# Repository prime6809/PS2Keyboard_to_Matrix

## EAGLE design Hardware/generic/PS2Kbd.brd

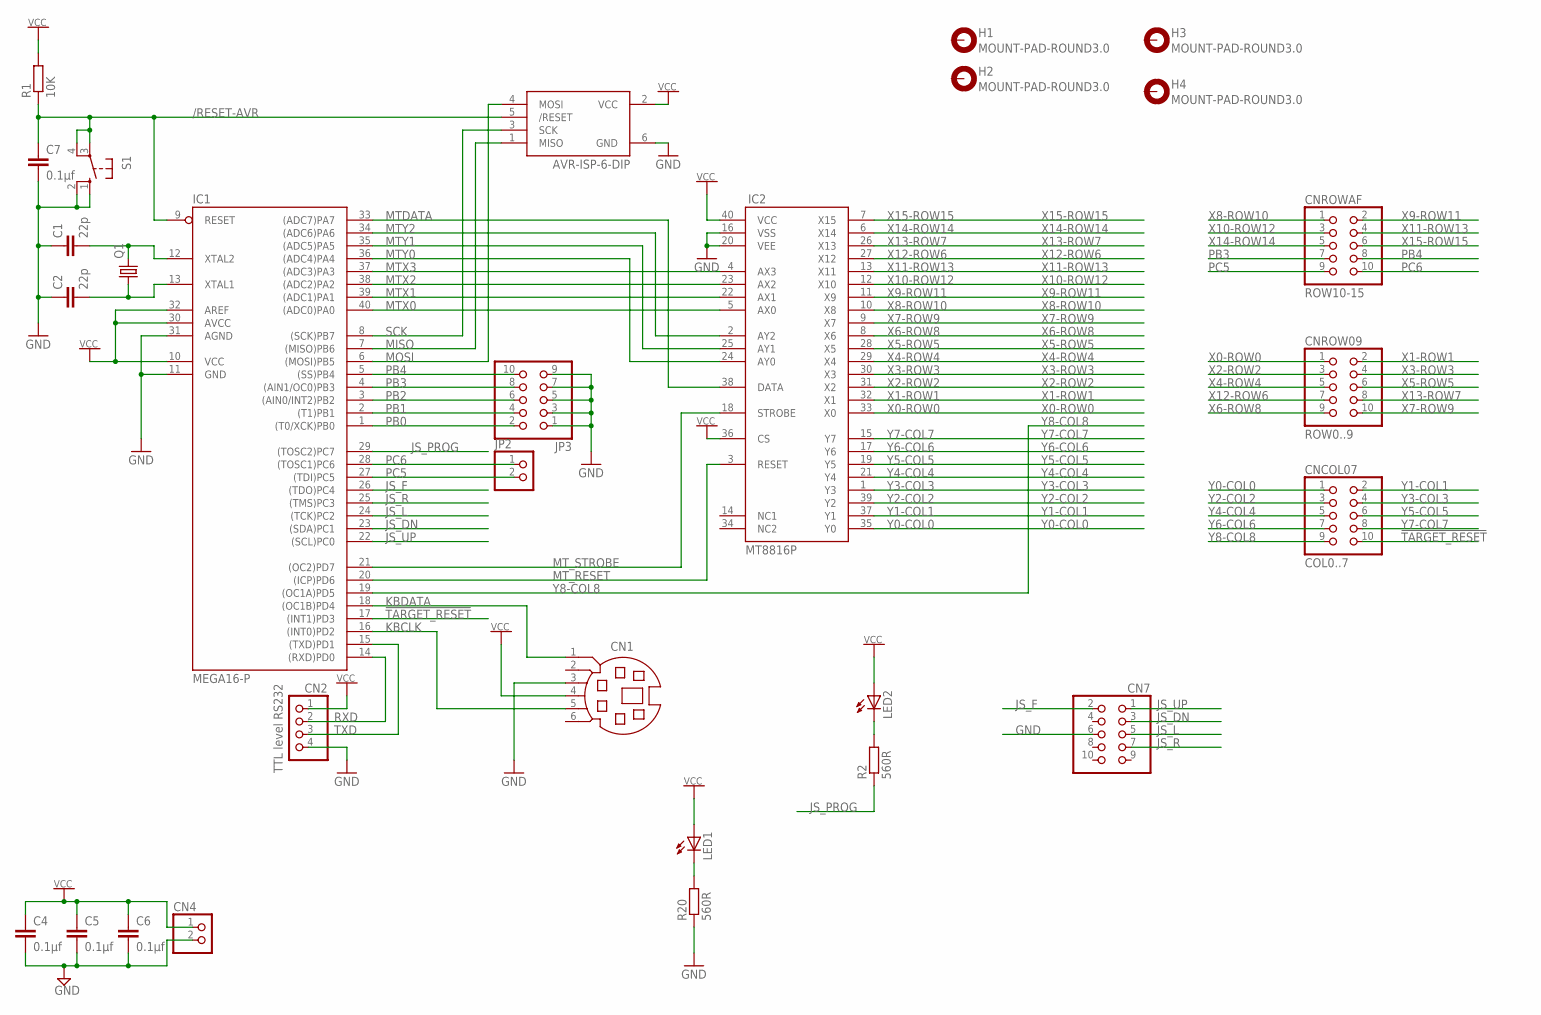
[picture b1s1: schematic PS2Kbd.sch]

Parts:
C1, C2: 22p; C025-025X050
C4, C5, C6, C7: 0.1µf; C025-025X050
CN1: MD06SS; MDIN06SS
CN2: PINHD-1X4; 1X04
CN3: AVR-ISP-6-DIP; 2X3
CN4: PINHD-1X2; 1X02
CN7: PINHD-2X5; 2X05
CNCOL07: COL0..7; 2X05
CNROW09: ROW0..9; 2X05
CNROWAF: ROW10-15; 2X05
H1, H2, H3, H4: MOUNT-PAD-ROUND3.0; 3,0-PAD
IC1: MEGA16-P; DIL40
IC2: MT8816P; DIL40
JP2: PINHD-1X2; 1X02
JP3: PINHD-2X5; 2X05
LED1, LED2: LED3MM
Q1: CRYSTALHC49S; HC49/S
R1: 10K; 0207/10
R2, R20: 560R; 0207/10
S1: 10-XX; B3F-10XX

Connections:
!TARGET_RESET: CNCOL07.10, IC1.17 ((INT1)PD3)
/RESET-AVR: C7.1, CN3.5 (/RESET), IC1.9 (RESET), R1.1, S1.3, S1.4 (P1)
GND: C1.1, C2.1, C4.2, C5.2, C6.2, C7.2, CN1.3, CN2.4, CN3.6 (GND), CN4.2, CN7.6, IC1.11 (GND), IC1.31 (AGND), IC2.16 (VSS), IC2.20 (VEE), JP3.1, JP3.3, JP3.5, JP3.7, JP3.9, R20.1, S1.1 (S), S1.2 (S1)
JS_DN: CN7.3, IC1.23 ((SDA)PC1)
JS_F: CN7.2, IC1.26 ((TDO)PC4)
JS_L: CN7.5, IC1.24 ((TCK)PC2)
JS_PROG: IC1.29 ((TOSC2)PC7), R2.1
JS_R: CN7.7, IC1.25 ((TMS)PC3)
JS_UP: CN7.1, IC1.22 ((SCL)PC0)
KBCLK: CN1.5, IC1.16 ((INT0)PD2)
KBDATA: CN1.1, IC1.18 ((OC1B)PD4)
MISO: CN3.1 (MISO), IC1.7 ((MISO)PB6)
MOSI: CN3.4 (MOSI), IC1.6 ((MOSI)PB5)
MTDATA: IC1.33 ((ADC7)PA7), IC2.38 (DATA)
MTX0: IC1.40 ((ADC0)PA0), IC2.5 (AX0)
MTX1: IC1.39 ((ADC1)PA1), IC2.22 (AX1)
MTX2: IC1.38 ((ADC2)PA2), IC2.23 (AX2)
MTX3: IC1.37 ((ADC3)PA3), IC2.4 (AX3)
MTY0: IC1.36 ((ADC4)PA4), IC2.24 (AY0)
MTY1: IC1.35 ((ADC5)PA5), IC2.25 (AY1)
MTY2: IC1.34 ((ADC6)PA6), IC2.2 (AY2)
MT_RESET: IC1.20 ((ICP)PD6), IC2.3 (RESET)
MT_STROBE: IC1.21 ((OC2)PD7), IC2.18 (STROBE)
unnamed: LED2.K (C), R2.2
unnamed: C1.2, IC1.12 (XTAL2), Q1.2
unnamed: C2.2, IC1.13 (XTAL1), Q1.1
unnamed: LED1.K (C), R20.2
PB0: IC1.1 ((T0/XCK)PB0), JP3.2
PB1: IC1.2 ((T1)PB1), JP3.4
PB2: IC1.3 ((AIN0/INT2)PB2), JP3.6
PB3: CNROWAF.7, IC1.4 ((AIN1/OC0)PB3), JP3.8
PB4: CNROWAF.8, IC1.5 ((SS)PB4), JP3.10
PC5: CNROWAF.9, IC1.27 ((TDI)PC5), JP2.2
PC6: CNROWAF.10, IC1.28 ((TOSC1)PC6), JP2.1
RXD: CN2.2, IC1.14 ((RXD)PD0)
SCK: CN3.3 (SCK), IC1.8 ((SCK)PB7)
TXD: CN2.3, IC1.15 ((TXD)PD1)
VCC: C4.1, C5.1, C6.1, CN1.4, CN2.1, CN3.2 (VCC), CN4.1, IC1.10 (VCC), IC1.30 (AVCC), IC1.32 (AREF), IC2.36 (CS), IC2.40 (VCC), LED1.A, LED2.A, R1.2
X0-ROW0: CNROW09.1, IC2.33 (X0)
X1-ROW1: CNROW09.2, IC2.32 (X1)
X2-ROW2: CNROW09.3, IC2.31 (X2)
X3-ROW3: CNROW09.4, IC2.30 (X3)
X4-ROW4: CNROW09.5, IC2.29 (X4)
X5-ROW5: CNROW09.6, IC2.28 (X5)
X6-ROW8: CNROW09.9, IC2.8 (X6)
X7-ROW9: CNROW09.10, IC2.9 (X7)
X8-ROW10: CNROWAF.1, IC2.10 (X8)
X9-ROW11: CNROWAF.2, IC2.11 (X9)
X10-ROW12: CNROWAF.3, IC2.12 (X10)
X11-ROW13: CNROWAF.4, IC2.13 (X11)
X12-ROW6: CNROW09.7, IC2.27 (X12)
X13-ROW7: CNROW09.8, IC2.26 (X13)
X14-ROW14: CNROWAF.5, IC2.6 (X14)
X15-ROW15: CNROWAF.6, IC2.7 (X15)
Y0-COL0: CNCOL07.1, IC2.35 (Y0)
Y1-COL1: CNCOL07.2, IC2.37 (Y1)
Y2-COL2: CNCOL07.3, IC2.39 (Y2)
Y3-COL3: CNCOL07.4, IC2.1 (Y3)
Y4-COL4: CNCOL07.5, IC2.21 (Y4)
Y5-COL5: CNCOL07.6, IC2.19 (Y5)
Y6-COL6: CNCOL07.7, IC2.17 (Y6)
Y7-COL7: CNCOL07.8, IC2.15 (Y7)
Y8-COL8: CNCOL07.9, IC1.19 ((OC1A)PD5)

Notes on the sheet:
TTL level RS232

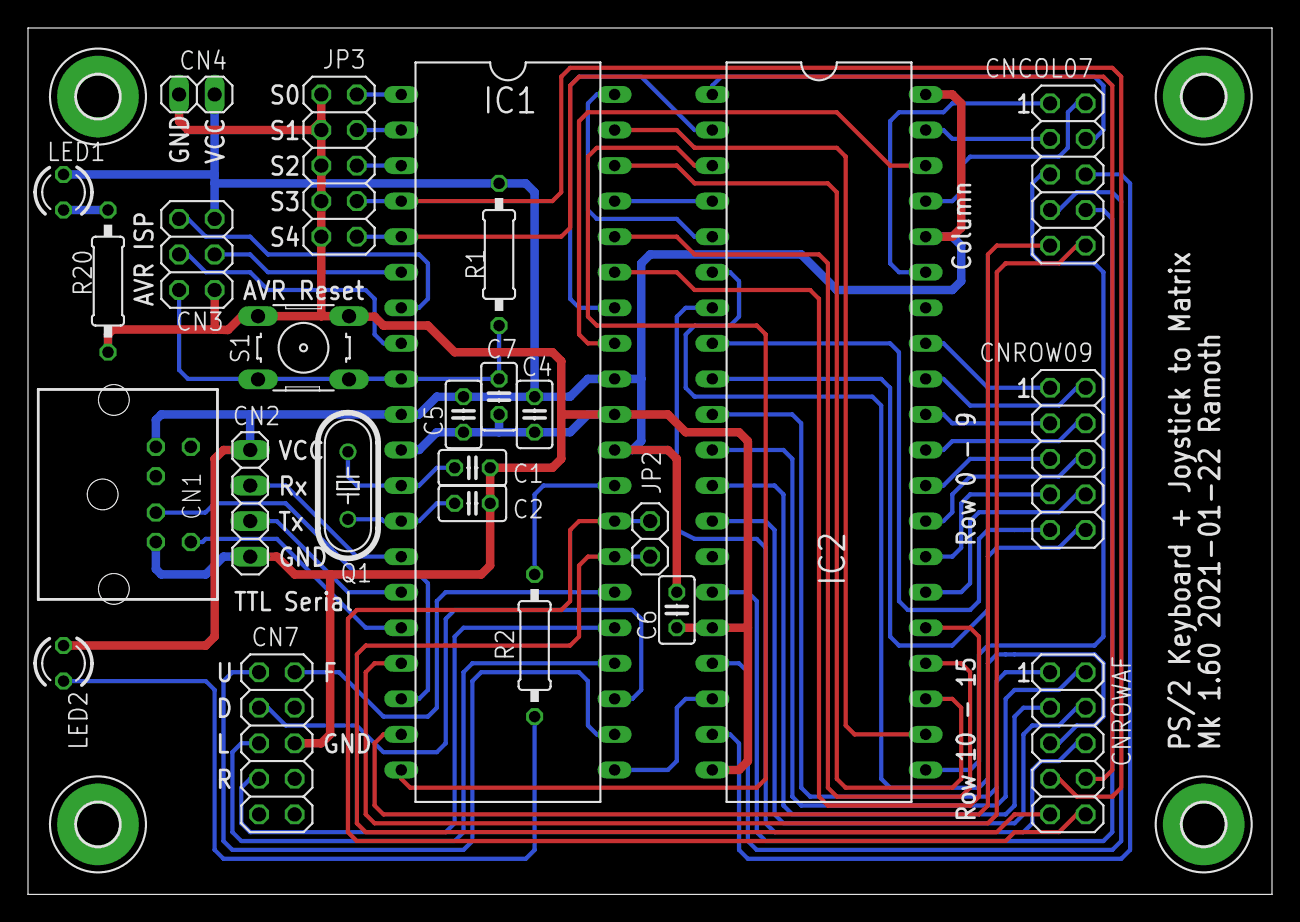
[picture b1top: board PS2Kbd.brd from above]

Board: 2 copper layers, 88.9 x 61.9 mm, 29 parts (0 on the bottom side), 63 nets.

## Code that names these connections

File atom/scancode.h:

/*
	Scancode table for the AtomClone keyboard interface. 

 PCScanCodeTo Acorn Atom keyboard emulation routines.

 Adapted from PCScanCodeTo Dragon, P.Harvey-Smith, 2008-12-06.
 
 The Atom keyboard data is then output to a Zarlink MT8816 8x16 
 crosspoint switch.

 The outputs of this crosspoint switch are then connected to the 
 Atom Row and column inputs, which are scanned by the Atom's 8255
 using port B1..7 (and C6) as pulled up inputs, and port A0..3
 as outputs connected to a 74LS45 or 74LS145, to select the row 
 to scan. This gives 10 rows and 9 columns, however, the 9th
 column only has one key connected to it, which is either grounded
 or pulled up (the REPT key), so this can just be driven by a spare
 AVR IO line.

 As the Atom has 10 rows, these will be connected to X0..9 of the 
 MT8816, and the columns to Y0..7 (and an IO line).

 The Atom keyboard is laid out as follows :-

74LS145	Keyboard columns								
Output		PB0		PB1		PB2		PB3		PB4		PB5		PB6		PB7 	PC6
0			        3		-		G		Q		Esc			
1			        2		,		F		P		Z			
2			U/D		1		;		E		O		Y			
3			L/R		0		:		D		N		X			
4			Lock	Del		9		C		M		W			
5			^		Copy	8		B		L		V			
6			]		Enter	7		A		K		U			
7			\				6		@		J		T			
8			[				5		/		I		S			
9			spc				4		.		H		R			
 									
 GND														Ctrl	Shift	Rept

Fot the following key definition constants, the high nibble and 0x70 represent the 
ROW of the pressed key, and the low nibble represents the COLUMN. Bit 7 is ignored, 
as this is used by the matrix handling code to flag a key pressed or released.
*/

#ifndef __SCANCODES__
#define __SCANCODES__

#include <inttypes.h>
#include <avr/pgmspace.h> 
#include "ps2scancode.h"
#include "matrix_kbd.h"

#define ATOM_KEY_UD			0x02
#define ATOM_KEY_LR			0x03
#define ATOM_KEY_LOCK		0x04
#define ATOM_KEY_CLARET		0x05
#define ATOM_KEY_RBRACK		0x06
#define ATOM_KEY_BSLASH		0x07
#define ATOM_KEY_LBRACK		0x08
#define ATOM_KEY_SPACE		0x09

#define ATOM_KEY_3			0x10
#define ATOM_KEY_2			0x11
#define ATOM_KEY_1			0x12
#define ATOM_KEY_0			0x13
#define ATOM_KEY_DELETE		0x14
#define ATOM_KEY_COPY		0x15
#define ATOM_KEY_ENTER		0x16

#define ATOM_KEY_MINUS		0x20
#define ATOM_KEY_COMMA		0x21
#define ATOM_KEY_SEMICOLON 	0x22
#define ATOM_KEY_COLON 		0x23
#define ATOM_KEY_9 			0x24
#define ATOM_KEY_8 			0x25
#define ATOM_KEY_7 			0x26
#define ATOM_KEY_6 			0x27
#define ATOM_KEY_5 			0x28
#define ATOM_KEY_4 			0x29

#define ATOM_KEY_G 			0x30
#define ATOM_KEY_F 			0x31
#define ATOM_KEY_E 			0x32
#define ATOM_KEY_D 			0x33
#define ATOM_KEY_C 			0x34
#define ATOM_KEY_B 			0x35
#define ATOM_KEY_A 			0x36
#define ATOM_KEY_AT 		0x37
#define ATOM_KEY_SLASH 		0x38
#define ATOM_KEY_POINT 		0x39

#define ATOM_KEY_Q 			0x40
#define ATOM_KEY_P 			0x41
#define ATOM_KEY_O 			0x42
#define ATOM_KEY_N 			0x43
#define ATOM_KEY_M 			0x44
#define ATOM_KEY_L 			0x45
#define ATOM_KEY_K 			0x46
#define ATOM_KEY_J 			0x47
#define ATOM_KEY_I 			0x48
#define ATOM_KEY_H 			0x49

#define ATOM_KEY_ESC 		0x50
#define ATOM_KEY_Z 			0x51
#define ATOM_KEY_Y 			0x52
#define ATOM_KEY_X 			0x53
#define ATOM_KEY_W 			0x54
#define ATOM_KEY_V 			0x55
#define ATOM_KEY_U 			0x56
#define ATOM_KEY_T 			0x57
#define ATOM_KEY_S 			0x58
#define ATOM_KEY_R			0x59

#define ATOM_KEY_CTRL 		0x6A
#define ATOM_KEY_SHIFT 		0x7A
#define ATOM_KEY_REPT 		0x8A

#define ATOM_KEY_BREAK		0xFF

#define SHIFT_KEY	ATOM_KEY_SHIFT
#define RESET_KEY	ATOM_KEY_BREAK


void ScancodeInit(matrix_t *ToInit);
#endif

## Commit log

2021-01-11 Initial commit of source and hardware docs.
2021-01-12 Updated building docs. Revised generic board.
2021-01-12 Test of ssh update, nothing to see here !
2021-01-12 Updated ignore for joe backups
2021-01-12 Fixed typo in building instructions.
2021-01-13 Updated TRS80 and Electron mappings.
2021-01-14 Test commit from work.
2021-01-14 Cleanup / removal of commented (no longer used) code
2021-01-17 Added target commodore, C64, C16, Plus 4, VIC-20. Various internal changes.
2021-01-17 Remove old folder
2021-01-18 Added definitions for numeric keypad for most targets.
2021-01-23 Moved target reset into common code. Implemented centralized initialization of jumpers, joystick and reset. Moved PS/2 LED handling into ps2kbd module. Added macros for setting / clearing LEDS.
2021-01-23 Fixed Dragon / CoCo matrix so all keys are produced. Added matrix dumping code.
2021-01-24 Added matrix dumping function, jumper S4 to enable. Made serial output dependednt on S3 being jumpered.
2021-02-22 Various small changes, added ESC as break on TRS80.
2021-02-27 Alternate matrix for TRS80, allowing 1:1 cable.
2021-02-27 Added separate tables for TRS80 Model 3 / Model 4 as the 3 doesn't have some of the keys the 4 has (CTRL, CAPS and 3 function keys).
    Added pdf schematic and gerbers for Generic version of hardware.
2021-02-28 Updated connections for TRS80, addeed documentation fors Jumpers
2022-03-24 Added config for Dragon Beta
2022-08-05 Added Dragon Beta matrix.
2024-06-10 Added support for the Amstrad CPC-6128.
2024-10-21 Removed redundant code and file.
2024-10-22 Added support for Apple IIc.
2024-10-22 Fixed the JSLEDOn macro.
2025-01-26 Added apple_iic and amstrad_cpc to cleanall script
